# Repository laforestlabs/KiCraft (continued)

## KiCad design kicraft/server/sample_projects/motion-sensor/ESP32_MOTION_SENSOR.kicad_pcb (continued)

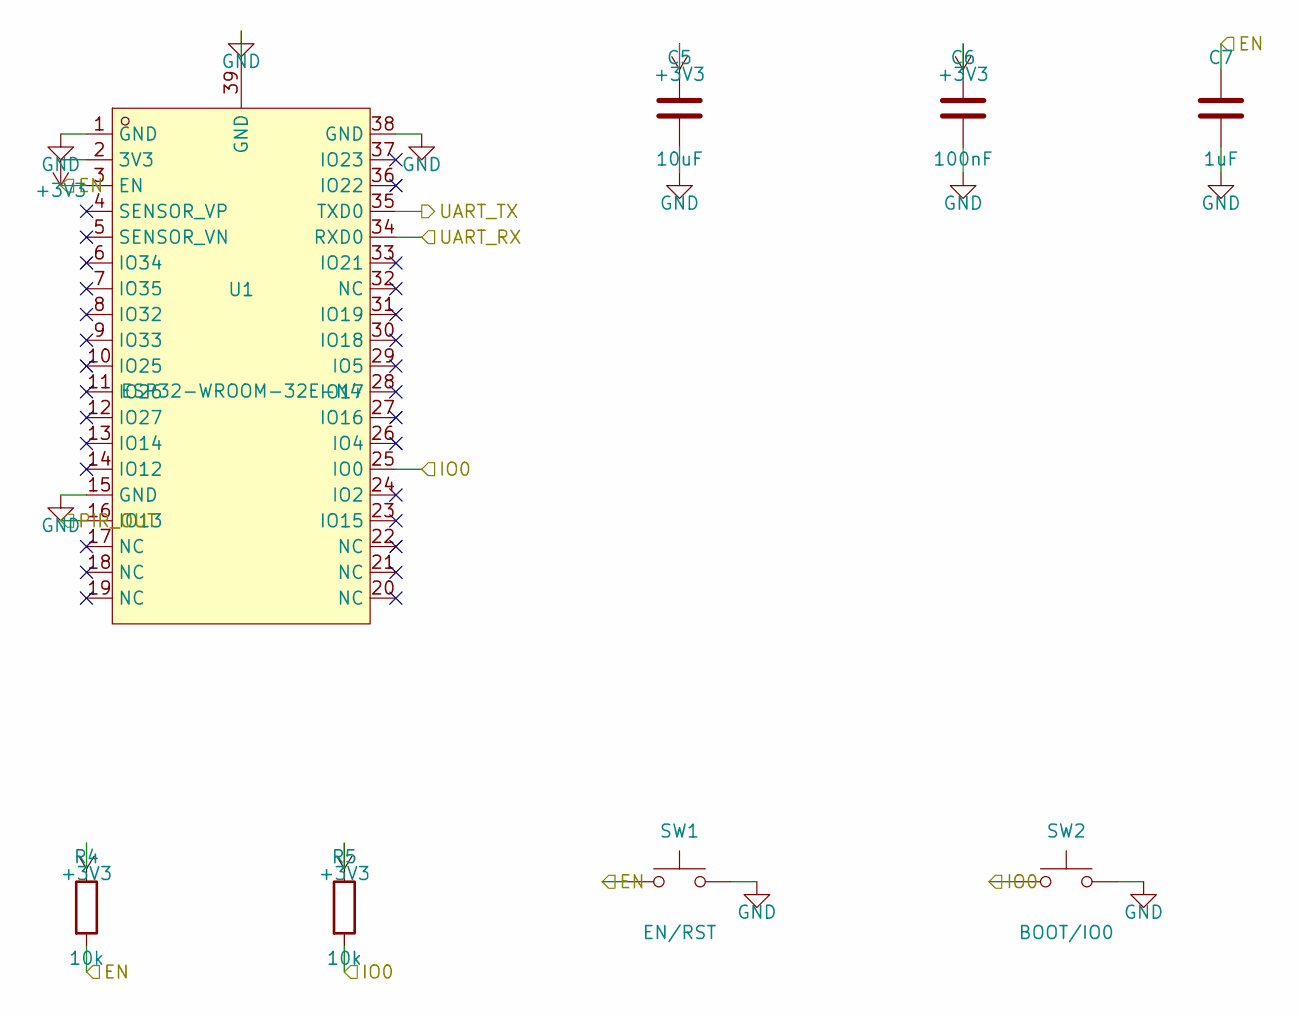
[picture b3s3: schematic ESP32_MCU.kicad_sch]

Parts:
C5: 10uF; C_0805_2012Metric
C6: 100nF; C_0603_1608Metric
C7: 1uF; C_0603_1608Metric
R4, R5: 10k; R_0603_1608Metric
SW1: EN/RST; SW_Push_1P1T_XKB_TS-1187A
SW2: BOOT/IO0; SW_Push_1P1T_XKB_TS-1187A
U1: ESP32-WROOM-32E-N4; WIFI-SMD_ESP32-WROOM-32E

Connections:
+3V3: C5.1, C6.1, R4.1, R5.1, U1.2 (3V3); also elsewhere on the board
EN: C7.1, R4.2, SW1.1, U1.3 (EN); also elsewhere on the board
IO0: R5.2, SW2.1, U1.25 (IO0); also elsewhere on the board
PIR_OUT: U1.16 (IO13); also elsewhere on the board
UART_RX: U1.34 (RXD0); also elsewhere on the board
UART_TX: U1.35 (TXD0); also elsewhere on the board

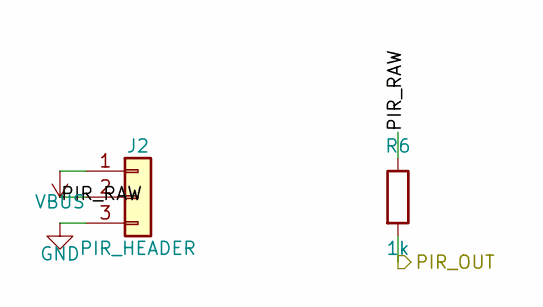
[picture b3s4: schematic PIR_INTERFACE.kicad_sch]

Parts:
J2: PIR_HEADER; PinHeader_1x03_P2.54mm_Vertical
R6: 1k; R_0603_1608Metric

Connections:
PIR_OUT: R6.2; also elsewhere on the board
PIR_RAW: J2.2, R6.1

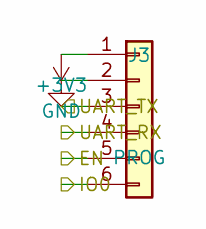
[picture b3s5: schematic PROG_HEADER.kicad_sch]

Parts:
J3: PROG; PinHeader_1x06_P2.54mm_Vertical

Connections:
+3V3: J3.1; also elsewhere on the board
EN: J3.5; also elsewhere on the board
IO0: J3.6; also elsewhere on the board
UART_RX: J3.4; also elsewhere on the board
UART_TX: J3.3; also elsewhere on the board

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
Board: 2 copper layers, 22 parts (0 on the bottom side), 12 nets, no tracks yet.

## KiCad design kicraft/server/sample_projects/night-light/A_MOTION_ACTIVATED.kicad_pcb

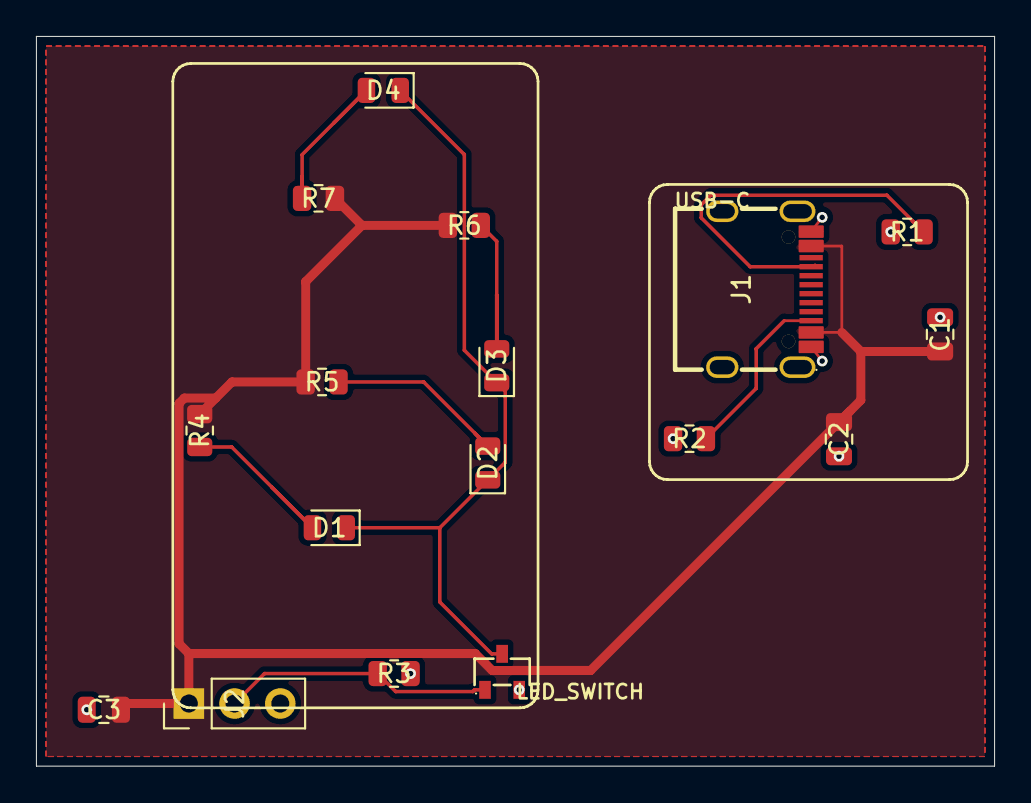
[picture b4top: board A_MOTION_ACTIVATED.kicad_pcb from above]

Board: 2 copper layers, 53.2 x 40.5 mm, 17 parts (0 on the bottom side), 10 nets.

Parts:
C1: 10uF; C_0805_2012Metric
C2, C3: 0.1uF; C_0805_2012Metric
D1, D2, D3, D4: Warm White LED; LED_0805_2012Metric
J1: USB-C Receptacle; USB-C_SMD-TYPE-C-31-M-12_1
J2: PinHeader_1x03; PinHeader_1x03_P2.54mm_Vertical
Q1: AO3400A; SOT-23-3_L2.9-W1.3-P1.90-LS2.4-BR
R1, R2: 5.1k; R_0805_2012Metric
R3: 10k; R_0805_2012Metric
R4, R5, R6, R7: 100; R_0805_2012Metric

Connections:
CC1: J1.A5, R1.1
CC2: J1.B5, R2.1
DRAIN: D1.1, D2.1, D3.1, D4.1, Q1.3
GND: C1.2, C2.2, C3.2, J1.1, J1.2, J1.3, J1.4, J1.A1B12, J1.B1A12, J2.3, Q1.2, R1.2, R2.2, R3.2
LED1_A: D1.2, R4.2
LED2_A: D2.2, R5.2
LED3_A: D3.2, R6.2
LED4_A: D4.2, R7.2
PIR_OUT: J2.2, Q1.1, R3.1
VBUS: C1.1, C2.1, C3.1, J1.A4B9, J1.B4A9, J2.1, R4.1, R5.1, R6.1, R7.1

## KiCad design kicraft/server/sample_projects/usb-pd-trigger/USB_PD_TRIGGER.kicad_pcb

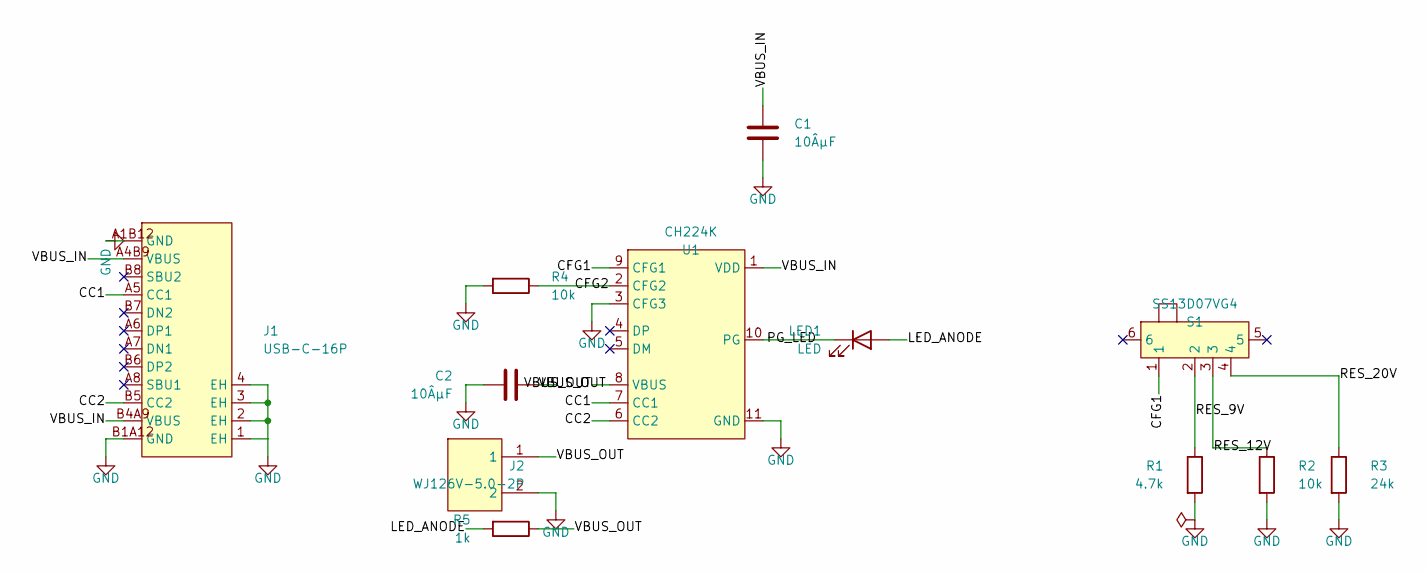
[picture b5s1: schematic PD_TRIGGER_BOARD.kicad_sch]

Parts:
C1, C2: 10ÂµF; C_0805_2012Metric
J1: USB-C-16P; USB-C_SMD-TYPE-C-31-M-12_1
J2: WJ126V-5.0-2P; CONN-TH_WJ126V-5.0-2P
LED1: LED; LED_0805_2012Metric
R1: 4.7k; R_0805_2012Metric
R2, R4: 10k; R_0805_2012Metric
R3: 24k; R_0805_2012Metric
R5: 1k; R_0805_2012Metric
S1: SS13D07VG4; SW-TH_SS13D07VG4
U1: CH224K; ESSOP-10_L4.9-W3.9-P1.0-LS6.0-TL-EP

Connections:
CC1: J1.A5 (CC1), U1.7 (CC1)
CC2: J1.B5 (CC2), U1.6 (CC2)
CFG1: S1.1, U1.9 (CFG1)
CFG2: R4.1, U1.2 (CFG2)
GND: C1.2, C2.2, J1.1 (EH), J1.2 (EH), J1.3 (EH), J1.4 (EH), J1.A1B12 (GND), J1.B1A12 (GND), J2.2, R1.2, R2.2, R3.2, R4.2, U1.3 (CFG3), U1.11 (GND)
LED_ANODE: LED1.2 (A), R5.2
PG_LED: LED1.1 (K), U1.10 (PG)
RES_9V: R1.1, S1.2
RES_12V: R2.1, S1.3
RES_20V: R3.1, S1.4
VBUS_IN: C1.1, J1.A4B9 (VBUS), J1.B4A9 (VBUS), U1.1 (VDD)
VBUS_OUT: C2.1, J2.1, R5.1, U1.8 (VBUS)

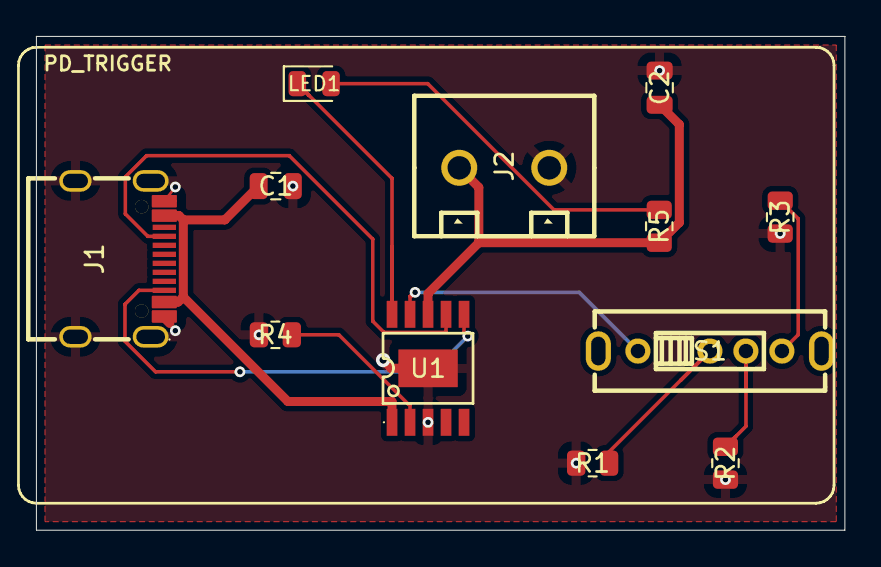
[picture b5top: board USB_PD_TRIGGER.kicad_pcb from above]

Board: 2 copper layers, 44.9 x 27.4 mm, 12 parts (0 on the bottom side), 12 nets.

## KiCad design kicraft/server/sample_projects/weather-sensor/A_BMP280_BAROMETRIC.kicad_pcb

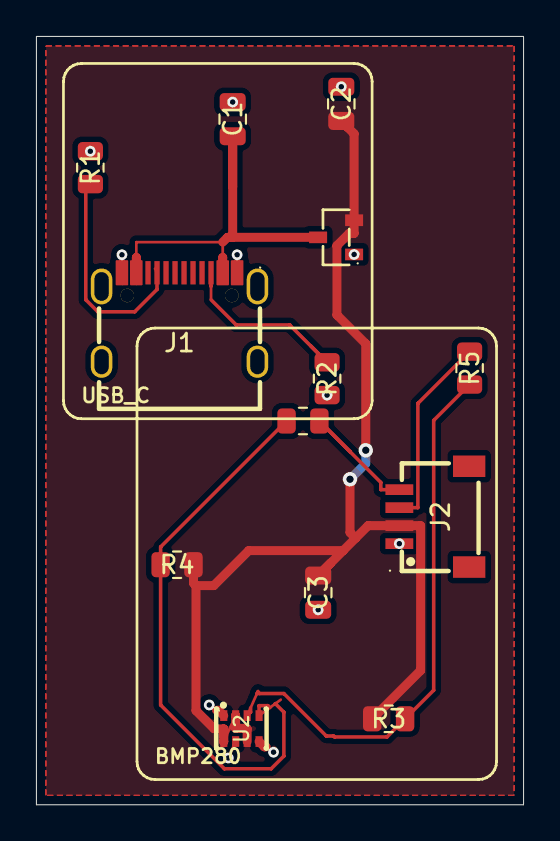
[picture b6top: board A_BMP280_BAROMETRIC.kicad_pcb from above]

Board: 2 copper layers, 27.1 x 42.7 mm, 13 parts (0 on the bottom side), 9 nets.

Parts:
C1, C2: 1ÂµF; C_0805_2012Metric
C3: 100nF; C_0805_2012Metric
J1: TYPE-C-31-M-12; USB-C_SMD-TYPE-C-31-M-12_1
J2: SM04B-SRSS-TB; CONN-SMD_4P-P1.00_SM04B-SRSS-TB-LF-SN
R1, R2: 5.1k; R_0805_2012Metric
R3, R4: 4.7k; R_0805_2012Metric
R5, R6: 10; R_0805_2012Metric
U1: 3.3V; SOT-23-3_L2.9-W1.3-P1.90-LS2.4-BR
U2: BMP280; LGA-8_L2.5-W2.0-P0.65_AMP6127

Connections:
+3V3: C2.1, C3.1, J2.2, R3.1, R4.1, U1.2, U2.2, U2.6, U2.8
CC1: J1.A5, R1.1
CC2: J1.B5, R2.1
GND: C1.2, C2.2, C3.2, J1.A1B12, J1.B1A12, J2.1, R1.2, R2.2, U1.1, U2.1, U2.5, U2.7
SCL: R4.2, R6.1, U2.4
SCL_QWIIC: J2.4, R6.2
SDA: R3.2, R5.1, U2.3
SDA_QWIIC: J2.3, R5.2
VBUS: C1.1, J1.A4B9, J1.B4A9, U1.3

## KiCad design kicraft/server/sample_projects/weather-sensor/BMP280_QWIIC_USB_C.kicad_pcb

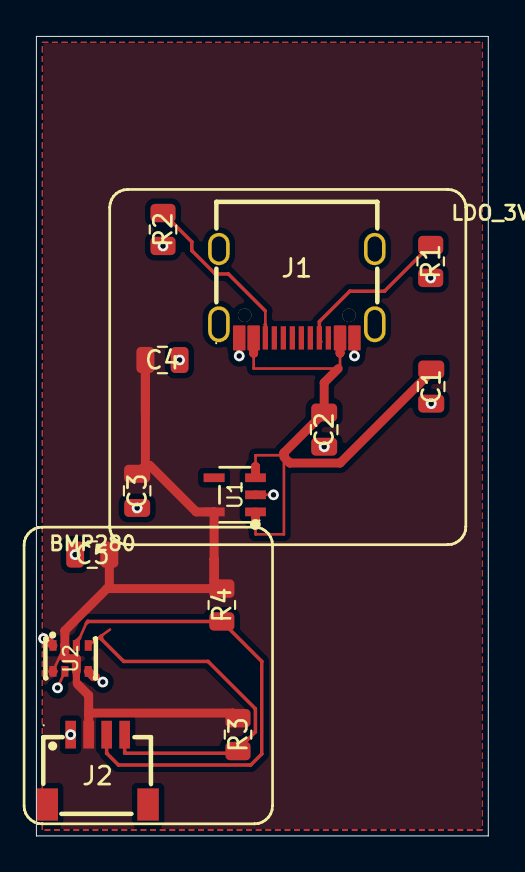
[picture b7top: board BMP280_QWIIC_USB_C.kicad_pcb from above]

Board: 2 copper layers, 25.1 x 44.4 mm, 13 parts (0 on the bottom side), 7 nets.

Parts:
C1, C2, C3, C4: 1ÂµF; C_0805_2012Metric
C5: 100nF; C_0805_2012Metric
J1: TYPE-C-31-M-12; USB-C_SMD-TYPE-C-31-M-12_1
J2: SM04B-SRSS-TB; CONN-SMD_4P-P1.00_SM04B-SRSS-TB-LF-SN
R1, R2: 5.1k; R_0805_2012Metric
R3, R4: 4.7k; R_0805_2012Metric
U1: 3.3V; SOT-23-5_L3.0-W1.7-P0.95-LS2.8-BL
U2: BMP280; LGA-8_L2.5-W2.0-P0.65_AMP6127

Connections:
+3V3: C3.1, C4.1, C5.1, J2.2, R3.1, R4.1, U1.5, U2.2, U2.6, U2.8
CC1: J1.A5, R1.1
CC2: J1.B5, R2.1
GND: C1.2, C2.2, C3.2, C4.2, C5.2, J1.A1B12, J1.B1A12, J2.1, R1.2, R2.2, U1.2, U2.1, U2.5, U2.7
I2C_SCL: J2.4, R3.2, U2.4
I2C_SDA: J2.3, R4.2, U2.3
VBUS: C1.1, C2.1, J1.A4B9, J1.B4A9, U1.1, U1.3

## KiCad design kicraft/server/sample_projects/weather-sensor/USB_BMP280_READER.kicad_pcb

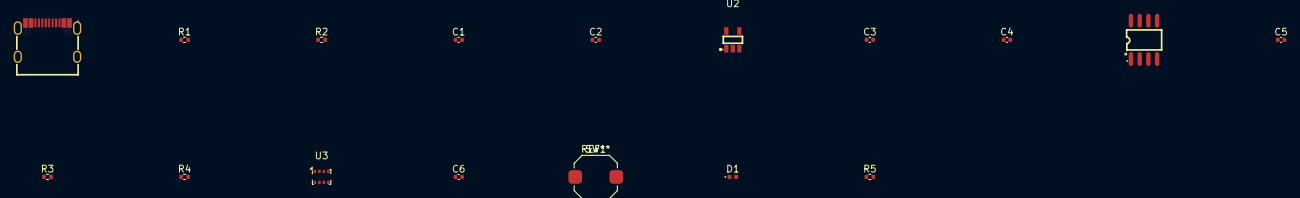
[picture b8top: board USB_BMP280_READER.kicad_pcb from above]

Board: 2 copper layers, 17 parts (0 on the bottom side), 10 nets, no tracks yet.

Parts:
C1: 4.7uF; C_0402_1005Metric
C2, C5, C6: 100nF; C_0402_1005Metric
C3, C4: 1uF; C_0402_1005Metric
D1: GREEN; LED_0402_1005Metric
J1: USB-C Receptacle; USB-C_SMD-TYPE-C-31-M-12_1
R1, R2: 5.1k; R_0402_1005Metric
R3, R4: 4.7k; R_0402_1005Metric
R5: 1k; R_0402_1005Metric
SW1: TACT; SW_Push_1TS009xxxx-xxxx-xxxx_6x6x5mm
U1: CH32V003J4M6; SOP-8_L4.9-W3.8-P1.27-LS6.0-BL
U2: AP2112K-3.3; SOT-25-5_L2.9-W1.6-P0.95-LS2.8-BL
U3: BMP280; Bosch_LGA-8_2x2.5mm_P0.65mm_ClockwisePinNumbering

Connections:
+3V3: C4.1, C5.1, C6.1, R3.1, R4.1, U1.4, U2.5, U3.2, U3.6, U3.8
BTN: SW1.1, U1.7
CC1: J1.A5, R1.1
CC2: J1.B5, R2.1
GND: C1.2, C2.2, C3.2, C4.2, C5.2, C6.2, D1.1, J1.1, J1.2, J1.3, J1.4, J1.A1B12, J1.B1A12, R1.2, R2.2, SW1.2, U1.2, U2.2, U3.1, U3.5, U3.7
LED: R5.1, U1.8
LED_ANODE: D1.2, R5.2
SCL: R4.2, U1.6, U3.4
SDA: R3.2, U1.5, U3.3
VBUS: C1.1, C2.1, C3.1, J1.A4B9, J1.B4A9, U2.1, U2.3
